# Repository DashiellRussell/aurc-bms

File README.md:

# AURC_BMS

Battery Management System for AURC (Australian Universities Rocket Competition).
Four-channel battery board set feeding two flight computers (FC1, FC2) and two pyro boards.
KiCad 10 project set.

## Layout

```
AURC_BMS/
├── libs/                     ← shared, single source of truth (all three boards point here)
│   ├── BMS.kicad_sym         ← symbols
│   ├── BMS.pretty/           ← footprints
│   └── 3dmodels/             ← .step / .wrl
├── docs/
│   ├── interconnect.md                ← the connector contract — READ THIS before touching a board edge
│   ├── architecture.md                ← full design rationale (living doc, currently v0.3)
│   └── board1_power_capture_plan.md   ← Board 1 schematic capture plan (sheets, netlist, BOM)
├── board1_power/             ← Board 1: USB-C, PD sink, 4× SY6970 smart charger, cells, ESP+I²C mux
├── board2_monitor/           ← Board 2: 64-LED gauge + driver, 4× pull-pin power-enable (spine)
├── board3_dist/              ← Board 3: passive fan-out to FC1+Pyro1 / FC2+Pyro2
└── _archive/                 ← previous single-board attempt (v0.1), kept for reference
```

Each `boardN_*/` is an independent KiCad project (`.kicad_pro` / `.kicad_sch` / `.kicad_pcb`) with
its own `sym-lib-table` + `fp-lib-table` that resolve the **shared** library at `../libs/` under
the nickname **`BMS`**. Add a part once in `libs/`; all three boards see it.

## Working on it

- **Before changing any board-to-board connector, edit `docs/interconnect.md` first.** It is the
  only thing keeping the three separately-laid-out boards mate-compatible.
- Add/edit symbols in `libs/BMS.kicad_sym`, footprints in `libs/BMS.pretty/`, 3D models in
  `libs/3dmodels/`. Don't make per-board copies — that defeats the single-source-of-truth setup.
- Open a board by opening its `boardN_*/boardN_*.kicad_pro`.

See `docs/architecture.md` for the full design (protection stack, charging, monitoring,
power-enable/safety, BOM, open items).

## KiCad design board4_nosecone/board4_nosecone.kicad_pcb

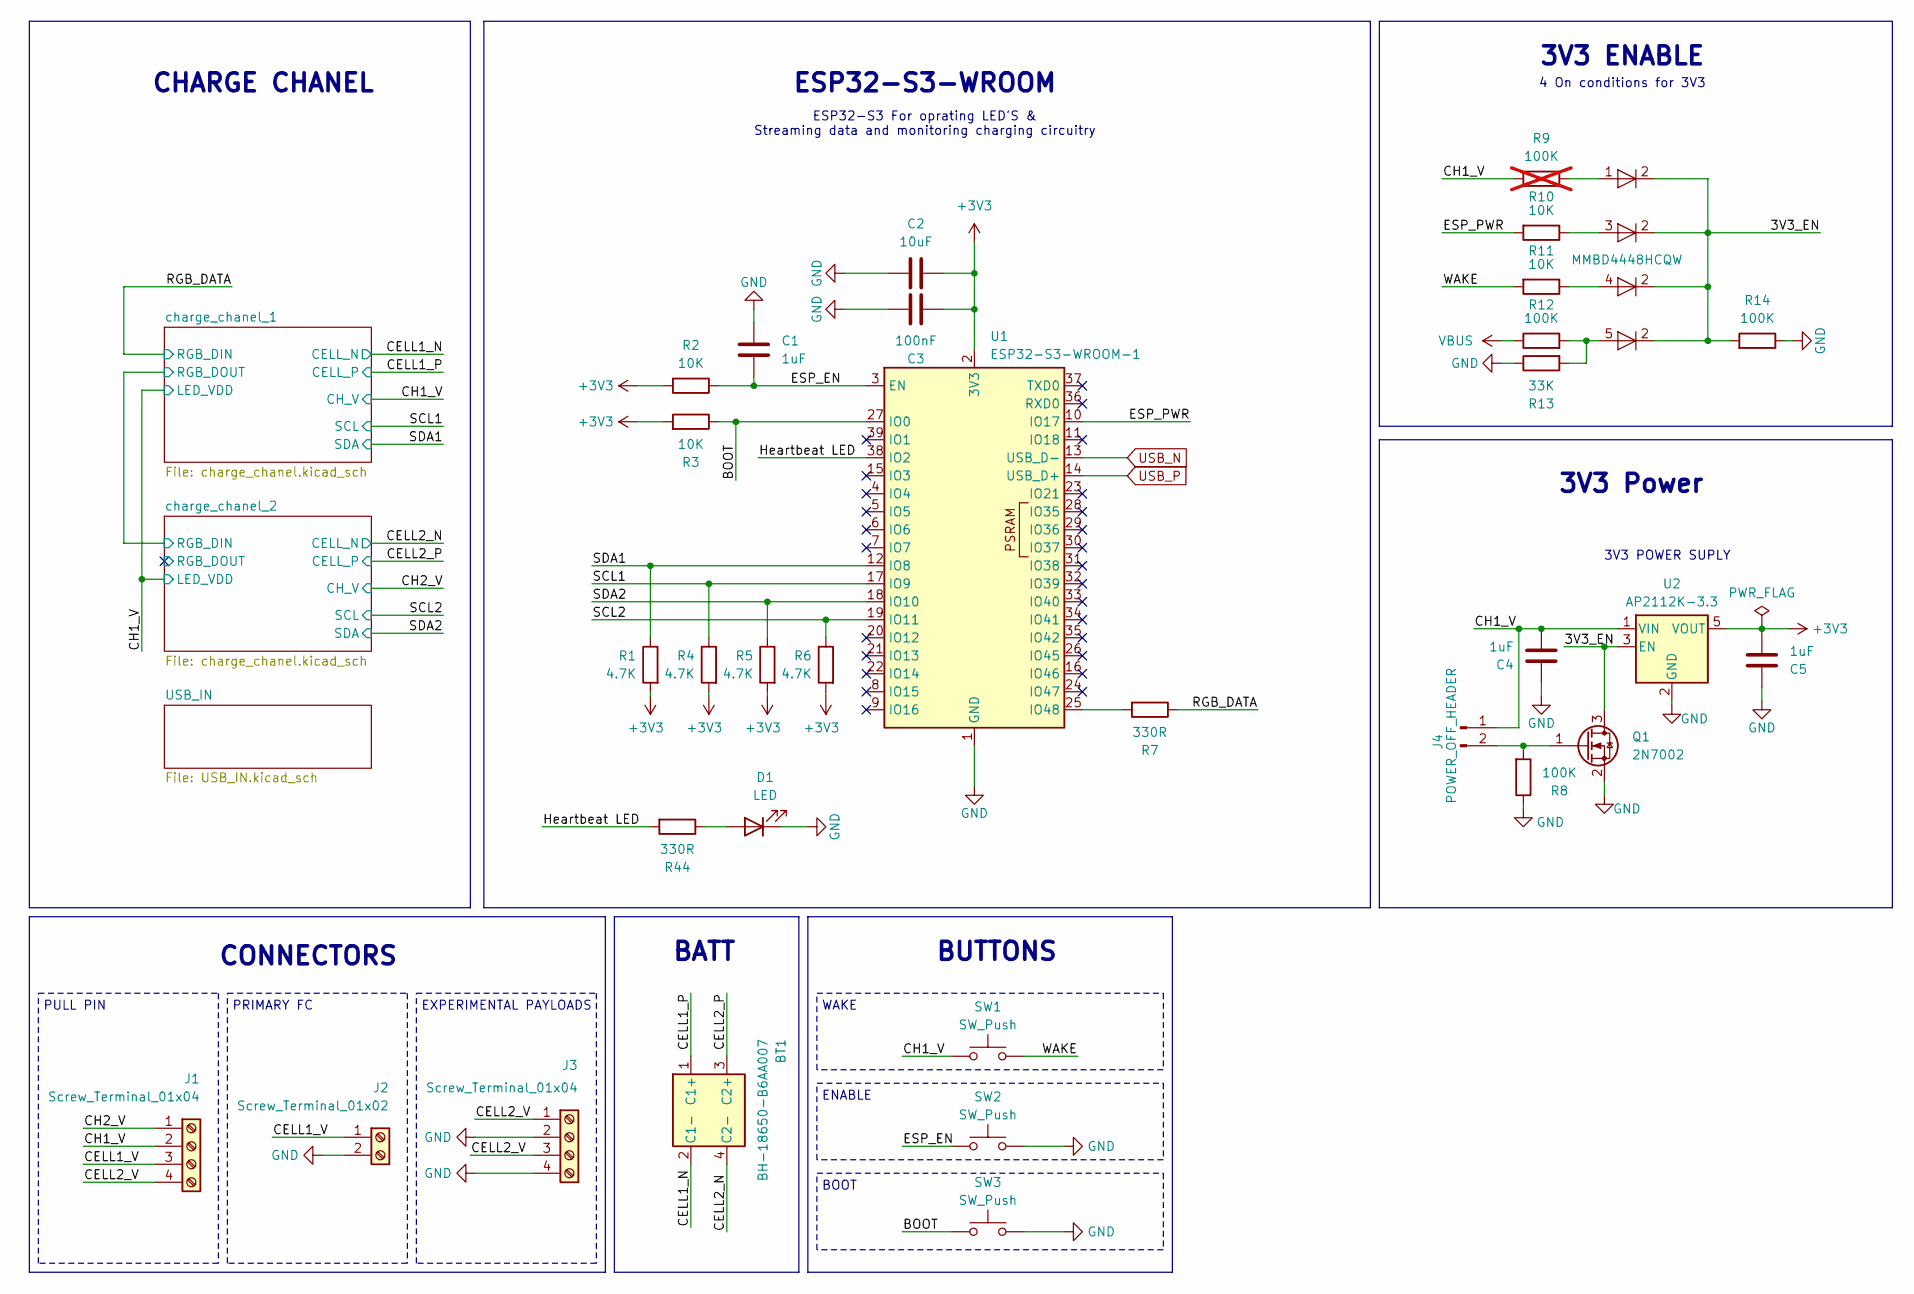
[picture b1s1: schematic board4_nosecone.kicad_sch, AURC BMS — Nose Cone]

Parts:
BT1: BH-18650-B6AA007
C1: 1uF; C_0603_1608Metric
C2: 10uF; C_0805_2012Metric
C3: 100nF; C_0805_2012Metric
C4, C5: 1uF; C_0805_2012Metric
D1: LED; LED_0603_1608Metric
D2: MMBD4448HCQW; SOT-353_SC-70-5
J1, J3: Screw_Terminal_01x04; TerminalBlock_Phoenix_PT-1,5-4-3.5-H_1x04_P3.50mm_Horizontal
J2: Screw_Terminal_01x02; TerminalBlock_Phoenix_PT-1,5-2-3.5-H_1x02_P3.50mm_Horizontal
J4: POWER_OFF_HEADER; PinHeader_1x02_P2.54mm_Horizontal
Q1: 2N7002; SOT-23
R1, R4, R5, R6: 4.7K; R_0603_1608Metric
R2, R3, R10, R11: 10K; R_0603_1608Metric
R7, R44: 330R; R_0603_1608Metric
R8, R12, R14: 100K; R_0603_1608Metric
R9: 100K; R_0603_1608Metric; not fitted
R13: 33K; R_0603_1608Metric
SW1, SW2, SW3: SW_Push; SW_Push_1P1T_NO_CK_KMR2
U1: ESP32-S3-WROOM-1
U2: AP2112K-3.3; SOT-23-5

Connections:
+3V3: C2.1, C3.1, C5.1, R1.2, R2.2, R3.2, R4.2, R5.2, R6.2, U1.2 (3V3), U2.5 (VOUT); also elsewhere on the board
/3V3_EN: D2.2 (K), Q1.3 (D), R14.2, U2.3 (EN)
/BOOT: R3.1, SW3.1, U1.27 (IO0)
/CELL1_N: BT1.2 (C1-); also elsewhere on the board
/CELL1_P: BT1.1 (C1+); also elsewhere on the board
/CELL1_V: J1.3, J2.1
/CELL2_N: BT1.4 (C2-); also elsewhere on the board
/CELL2_P: BT1.3 (C2+); also elsewhere on the board
/CELL2_V: J1.4, J3.1, J3.3
/CH1_V: C4.1, J1.2, J4.1, R9.1, SW1.1, U2.1 (VIN); also elsewhere on the board
/CH2_V: J1.1; also elsewhere on the board
/ESP_EN: C1.2, R2.1, SW2.1, U1.3 (EN)
/ESP_PWR: R10.2, U1.10 (IO17)
/Heartbeat LED: R44.2, U1.38 (IO2)
/RGB_DATA: R7.1; also elsewhere on the board
/SCL1: R4.1, U1.17 (IO9); also elsewhere on the board
/SCL2: R6.1, U1.19 (IO11); also elsewhere on the board
/SDA1: R1.1, U1.12 (IO8); also elsewhere on the board
/SDA2: R5.1, U1.18 (IO10); also elsewhere on the board
/WAKE: R11.2, SW1.2
GND: C1.1, C2.2, C3.2, C4.2, C5.2, D1.1 (K), J2.2, J3.2, J3.4, Q1.2 (S), R8.1, R13.1, R14.1, SW2.2, SW3.2, U1.1 (GND), U1.40 (GND), U1.41 (GND), U2.2 (GND); also elsewhere on the board
unnamed: D1.2 (A), R44.1
unnamed: D2.1 (A), R9.2
unnamed: D2.3 (A), R10.1
unnamed: D2.4 (A), R11.1
unnamed: D2.5 (A), R12.2, R13.2
unnamed: J4.2, Q1.1 (G), R8.2
unnamed: R7.2, U1.25 (IO48)
USB_N: U1.13 (USB_D-); also elsewhere on the board
USB_P: U1.14 (USB_D+); also elsewhere on the board
VBUS: R12.1; also elsewhere on the board

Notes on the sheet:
BUTTONS
CHARGE CHANEL
3V3 Power
4 On conditions for 3V3
ESP32-S3 For oprating LED'S & Streaming data and monitoring charging circuitry
ESP32-S3-WROOM
ENABLE
3V3 POWER SUPLY
PRIMARY FC
3V3 ENABLE
EXPERIMENTAL PAYLOADS
BATT
CONNECTORS
PULL PIN
BOOT
WAKE

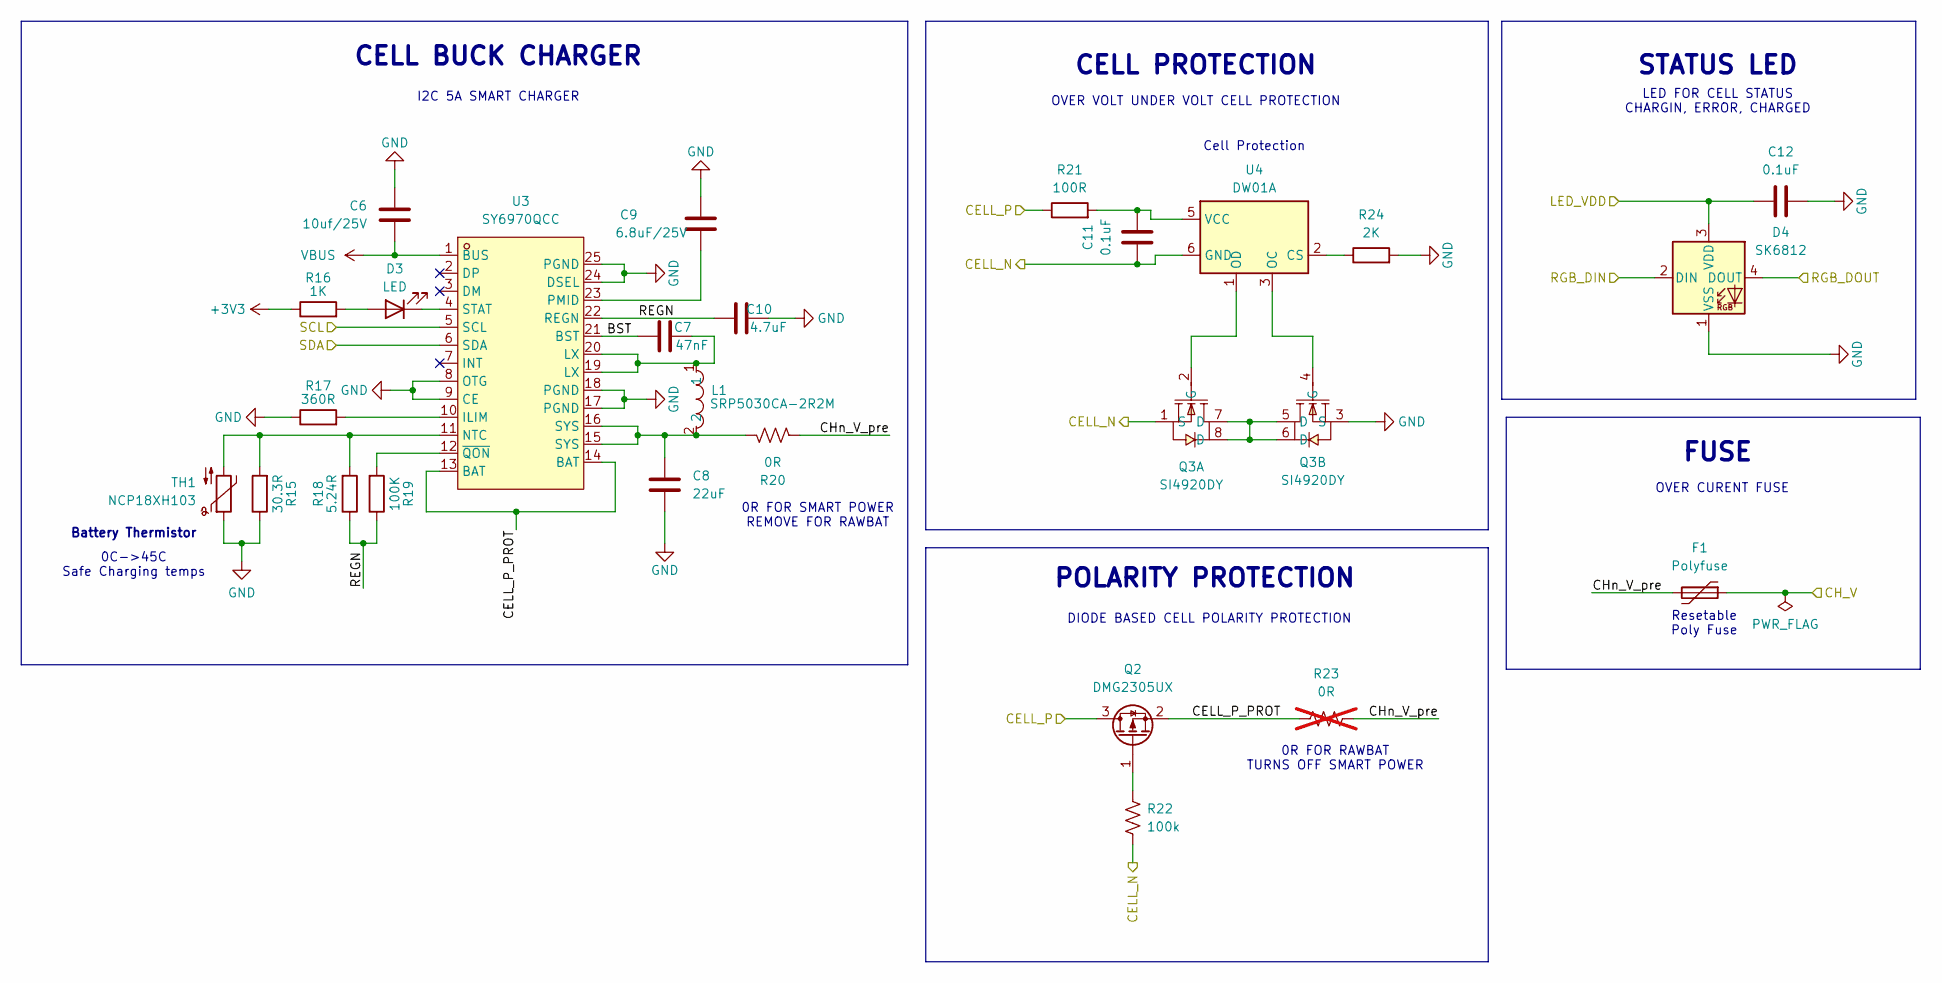
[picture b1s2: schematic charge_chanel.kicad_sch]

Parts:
C6: 10uf/25V; C_1206_3216Metric
C7: 47nF; C_0805_2012Metric
C8: 22uF; C_1206_3216Metric
C9: 6.8uF/25V; C_0805_2012Metric
C10: 4.7uF; C_0805_2012Metric
C11, C12: 0.1uF; C_0603_1608Metric
D3: LED; LED_0603_1608Metric
D4: SK6812; LED_SK6812_PLCC4_5.0x5.0mm_P3.2mm
F1: Polyfuse; Fuse_1812_4532Metric
L1: SRP5030CA-2R2M; IND-SMD_L5.5-W5.3; MPN SRP5030CA-2R2M; LCSC Part C2046809
Q2: DMG2305UX; SOT-23
Q3: SI4920DY; SOIC-8_L4.9-W3.9-P1.27-LS6.2-BL; MPN SI4920DY; LCSC Part C3289759
R15: 30.3R; R_0603_1608Metric
R16: 1K; R_0603_1608Metric
R17: 360R; R_0603_1608Metric
R18: 5.24R; R_0603_1608Metric
R19: 100K; R_0603_1608Metric
R20: 0R; R_2010_5025Metric
R21: 100R; R_0603_1608Metric
R22: 100k; R_0603_1608Metric
R23: 0R; R_2010_5025Metric; not fitted
R24: 2K; R_0603_1608Metric
TH1: NCP18XH103; R_0603_1608Metric
U3: SY6970QCC; QFN-24_L4.0-W4.0-P0.50-TL-EP2.7; MPN SY6970QCC; LCSC Part C5357542
U4: DW01A; SOT-23-6

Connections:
+3V3: R16.1; also elsewhere on the board
/CELL1_N: C11.1, Q3.1 (S), R22.1, U4.6 (GND); also elsewhere on the board
/CELL1_P: Q2.3 (D), R21.1; also elsewhere on the board
/CH1_V: C12.2, D4.3 (VDD), F1.1; also elsewhere on the board
/RGB_DATA: D4.2 (DIN); also elsewhere on the board
/SCL1: U3.5 (SCL); also elsewhere on the board
/SDA1: U3.6 (SDA); also elsewhere on the board
/charge_chanel_1/BST: C7.2, U3.21 (BST)
/charge_chanel_1/CELL_P_PROT: Q2.2 (S), R23.2, U3.13 (BAT), U3.14 (BAT)
/charge_chanel_1/CHn_V_pre: F1.2, R20.1, R23.1
/charge_chanel_1/REGN: C10.2, R18.1, R19.1, U3.22 (REGN)
/charge_chanel_1/RGB_DOUT: D4.4 (DOUT); also elsewhere on the board
GND: C6.1, C8.2, C9.1, C10.1, C12.1, D4.1 (VSS), Q3.3 (S), R15.1, R17.1, R24.2, TH1.1, U3.8 (OTG), U3.9 (CE), U3.17 (PGND), U3.18 (PGND), U3.24 (DSEL), U3.25 (PGND); also elsewhere on the board
unnamed: C7.1, L1.1, U3.19 (LX), U3.20 (LX)
unnamed: C8.1, L1.2, R20.2, U3.15 (SYS), U3.16 (SYS)
unnamed: D3.2 (A), R16.2
unnamed: D3.1 (K), U3.4 (STAT)
unnamed: Q2.1 (G), R22.2
unnamed: Q3.5 (D), Q3.6 (D), Q3.7 (D), Q3.8 (D)
unnamed: Q3.2 (G), U4.1 (OD)
unnamed: Q3.4 (G), U4.3 (OC)
unnamed: R17.2, U3.10 (ILIM)
unnamed: R15.2, R18.2, TH1.2, U3.11 (NTC)
unnamed: C9.2, U3.23 (PMID)
unnamed: R19.2, U3.12 (~QON)
unnamed: R24.1, U4.2 (CS)
unnamed: C11.2, R21.2, U4.5 (VCC)
VBUS: C6.2, U3.1 (BUS); also elsewhere on the board

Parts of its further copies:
C15: 10uf/25V; C_1206_3216Metric
C16: 47nF; C_0805_2012Metric
C17: 22uF; C_1206_3216Metric
C18: 6.8uF/25V; C_0805_2012Metric
C19: 4.7uF; C_0805_2012Metric
C20, C21: 0.1uF; C_0603_1608Metric
D6: LED; LED_0603_1608Metric
D7: SK6812; LED_SK6812_PLCC4_5.0x5.0mm_P3.2mm
F2: Polyfuse; Fuse_1812_4532Metric
L2: SRP5030CA-2R2M; IND-SMD_L5.5-W5.3; MPN SRP5030CA-2R2M; LCSC Part C2046809
Q4: DMG2305UX; SOT-23
Q5: SI4920DY; SOIC-8_L4.9-W3.9-P1.27-LS6.2-BL; MPN SI4920DY; LCSC Part C3289759
R34: 30.3R; R_0603_1608Metric
R35: 1K; R_0603_1608Metric
R36: 360R; R_0603_1608Metric
R37: 5.24R; R_0603_1608Metric
R38: 100K; R_0603_1608Metric
R39: 0R; R_2010_5025Metric
R40: 100R; R_0603_1608Metric
R41: 100k; R_0603_1608Metric
R42: 0R; R_2010_5025Metric; not fitted
R43: 2K; R_0603_1608Metric
TH2: NCP18XH103; R_0603_1608Metric
U7: SY6970QCC; QFN-24_L4.0-W4.0-P0.50-TL-EP2.7; MPN SY6970QCC; LCSC Part C5357542
U8: DW01A; SOT-23-6

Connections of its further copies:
+3V3: R35.1; also elsewhere on the board
/CELL2_N: C20.1, Q5.1 (S), R41.1, U8.6 (GND); also elsewhere on the board
/CELL2_P: Q4.3 (D), R40.1; also elsewhere on the board
/CH1_V: C21.2, D7.3 (VDD); also elsewhere on the board
/CH2_V: F2.1; also elsewhere on the board
/SCL2: U7.5 (SCL); also elsewhere on the board
/SDA2: U7.6 (SDA); also elsewhere on the board
/charge_chanel_1/RGB_DOUT: D7.2 (DIN); also elsewhere on the board
/charge_chanel_2/BST: C16.2, U7.21 (BST)
/charge_chanel_2/CELL_P_PROT: Q4.2 (S), R42.2, U7.13 (BAT), U7.14 (BAT)
/charge_chanel_2/CHn_V_pre: F2.2, R39.1, R42.1
/charge_chanel_2/REGN: C19.2, R37.1, R38.1, U7.22 (REGN)
/charge_chanel_2/RGB_DOUT: D7.4 (DOUT)
GND: C15.1, C17.2, C18.1, C19.1, C21.1, D7.1 (VSS), Q5.3 (S), R34.1, R36.1, R43.2, TH2.1, U7.8 (OTG), U7.9 (CE), U7.17 (PGND), U7.18 (PGND), U7.24 (DSEL), U7.25 (PGND); also elsewhere on the board
unnamed: C16.1, L2.1, U7.19 (LX), U7.20 (LX)
unnamed: C17.1, L2.2, R39.2, U7.15 (SYS), U7.16 (SYS)
unnamed: D6.2 (A), R35.2
unnamed: D6.1 (K), U7.4 (STAT)
unnamed: Q4.1 (G), R41.2
unnamed: Q5.5 (D), Q5.6 (D), Q5.7 (D), Q5.8 (D)
unnamed: Q5.2 (G), U8.1 (OD)
unnamed: Q5.4 (G), U8.3 (OC)
unnamed: R36.2, U7.10 (ILIM)
unnamed: R34.2, R37.2, TH2.2, U7.11 (NTC)
unnamed: C18.2, U7.23 (PMID)
unnamed: R38.2, U7.12 (~QON)
unnamed: R43.1, U8.2 (CS)
unnamed: C20.2, R40.2, U8.5 (VCC)
VBUS: C15.2, U7.1 (BUS); also elsewhere on the board

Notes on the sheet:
OVER VOLT UNDER VOLT CELL PROTECTION
CELL PROTECTION
0R FOR RAWBAT TURNS OFF SMART POWER
POLARITY PROTECTION
STATUS LED
Battery Thermistor
0C->45C Safe Charging temps
0R FOR SMART POWER REMOVE FOR RAWBAT
OVER CURENT FUSE
FUSE
Cell Protection
DIODE BASED CELL POLARITY PROTECTION
I2C 5A SMART CHARGER
CELL BUCK CHARGER
LED FOR CELL STATUS CHARGIN, ERROR, CHARGED
Resetable Poly Fuse

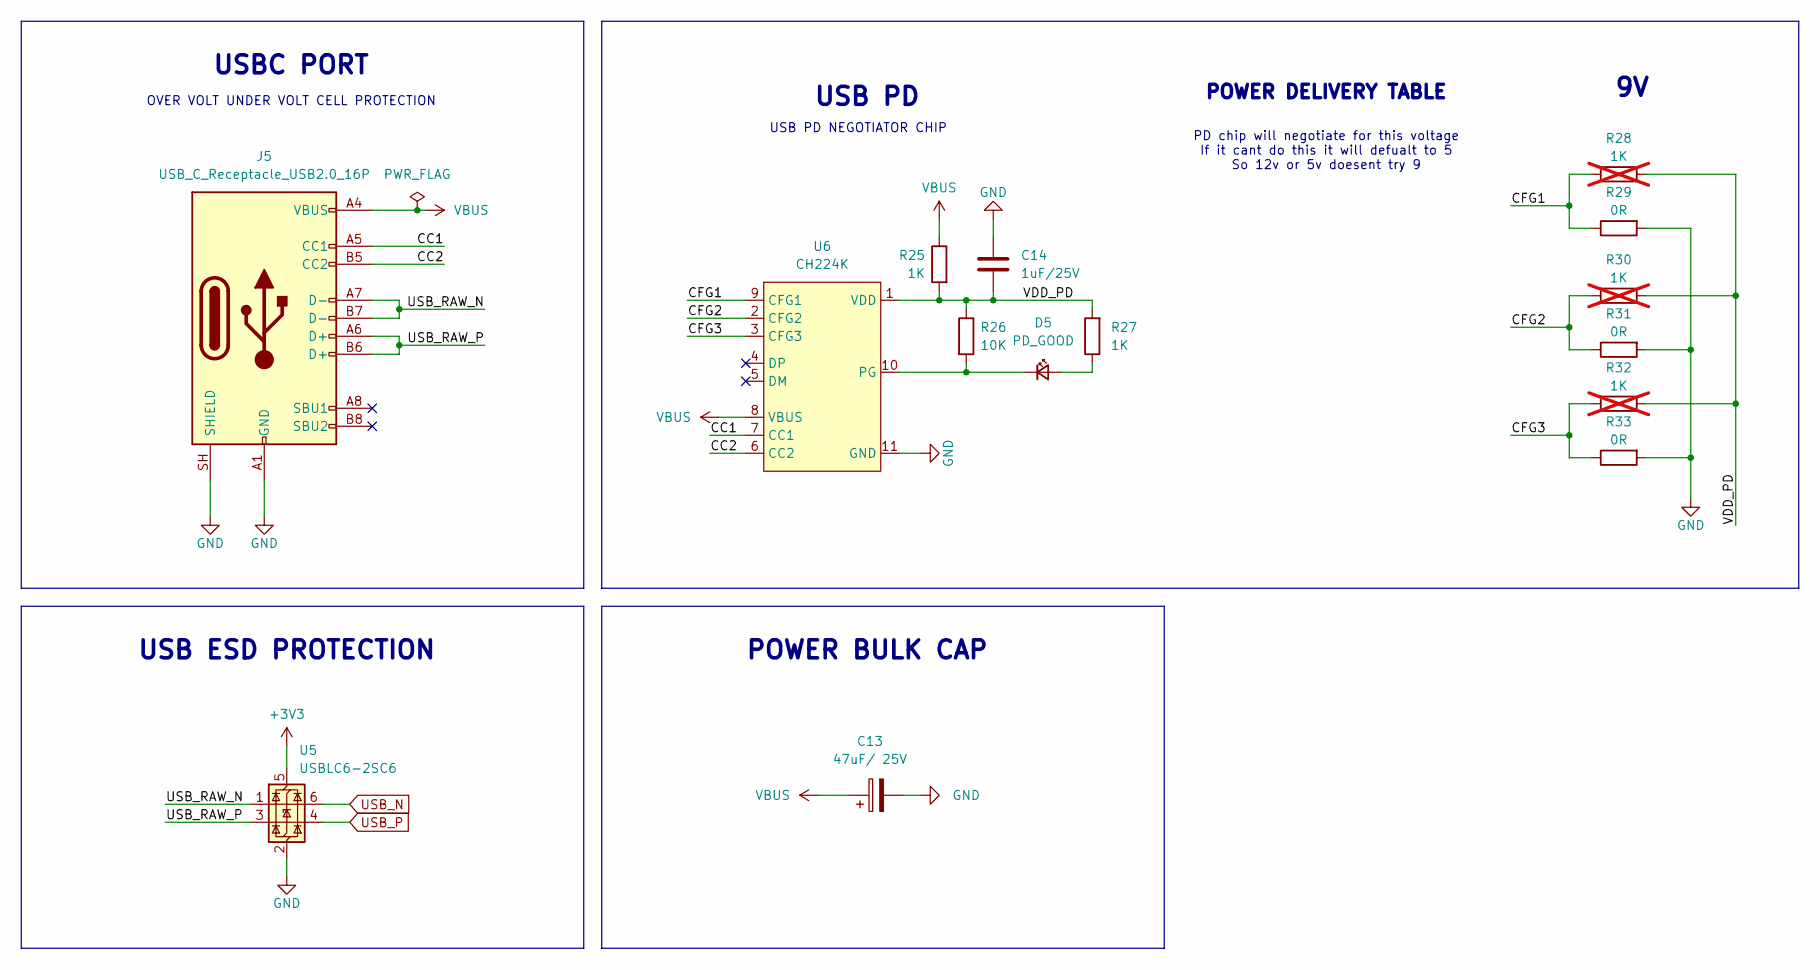
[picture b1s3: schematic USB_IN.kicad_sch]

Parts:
C13: 47uF/ 25V; CP_Elec_6.3x5.4
C14: 1uF/25V; C_0603_1608Metric
D5: PD_GOOD; LED_0603_1608Metric_Green
J5: USB_C_Receptacle_USB2.0_16P; USB_C_Receptacle_GCT_USB4105-xx-A_16P_TopMnt_Horizontal
R25: 1K; R_0805_2012Metric
R26: 10K; R_0603_1608Metric
R27: 1K; R_0603_1608Metric
R28, R30, R32: 1K; R_0805_2012Metric; not fitted
R29, R31, R33: 0R; R_0805_2012Metric
U5: USBLC6-2SC6; SOT-23-6
U6: CH224K; ESSOP-10_L4.9-W3.9-P1.0-LS6.0-TL-EP; MPN CH224K; LCSC Part C970725

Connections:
+3V3: U5.5 (VBUS); also elsewhere on the board
/USB_IN/CC1: J5.A5 (CC1), U6.7 (CC1)
/USB_IN/CC2: J5.B5 (CC2), U6.6 (CC2)
/USB_IN/CFG1: R28.2, R29.1, U6.9 (CFG1)
/USB_IN/CFG2: R30.2, R31.1, U6.2 (CFG2)
/USB_IN/CFG3: R32.2, R33.1, U6.3 (CFG3)
/USB_IN/USB_RAW_N: J5.A7 (D-), J5.B7 (D-), U5.1 (I/O1)
/USB_IN/USB_RAW_P: J5.A6 (D+), J5.B6 (D+), U5.3 (I/O2)
/USB_IN/VDD_PD: C14.2, R25.2, R26.1, R27.2, R28.1, R30.1, R32.1, U6.1 (VDD)
GND: C13.2, C14.1, J5.A1 (GND), J5.A12 (GND), J5.B1 (GND), J5.B12 (GND), J5.SH (SHIELD), R29.2, R31.2, R33.2, U5.2 (GND), U6.11 (GND); also elsewhere on the board
unnamed: D5.2 (A), R27.1
unnamed: D5.1 (K), R26.2, U6.10 (PG)
USB_N: U5.6 (I/O1); also elsewhere on the board
USB_P: U5.4 (I/O2); also elsewhere on the board
VBUS: C13.1, J5.A4 (VBUS), J5.A9 (VBUS), J5.B4 (VBUS), J5.B9 (VBUS), R25.1, U6.8 (VBUS); also elsewhere on the board

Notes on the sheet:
OVER VOLT UNDER VOLT CELL PROTECTION
USB ESD PROTECTION
USBC PORT
USB PD
POWER BULK CAP
PD chip will negotiate for this voltage If it cant do this it will defualt to 5 So 12v or 5v doesent try 9
USB PD NEGOTIATOR CHIP
POWER DELIVERY TABLE

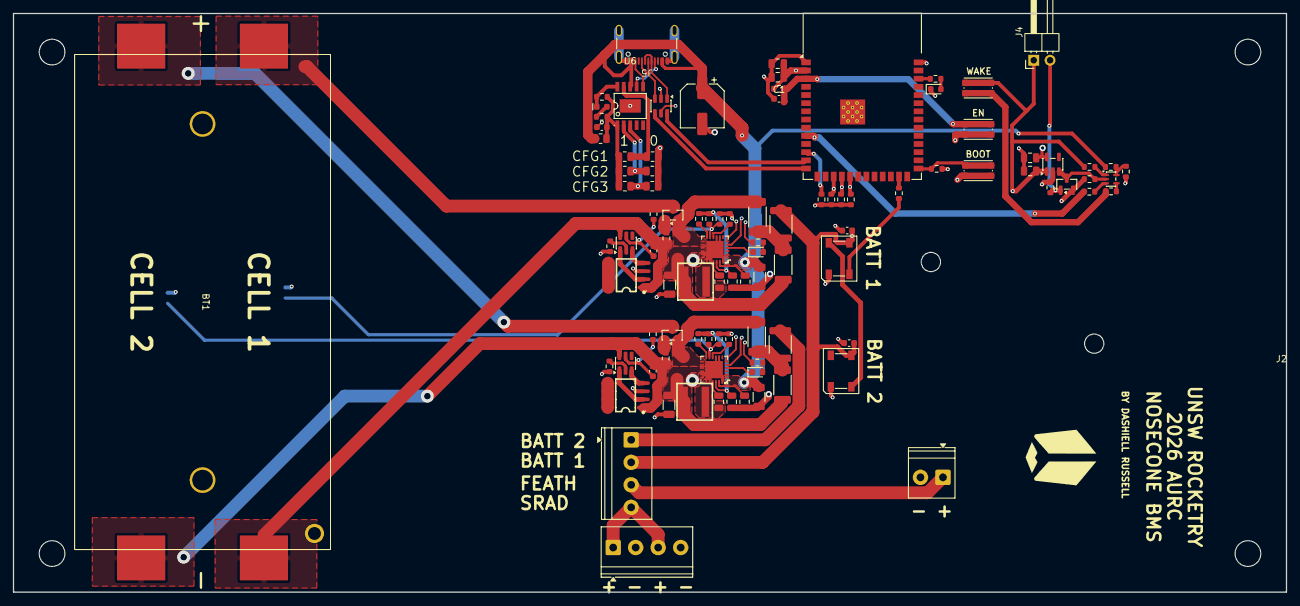
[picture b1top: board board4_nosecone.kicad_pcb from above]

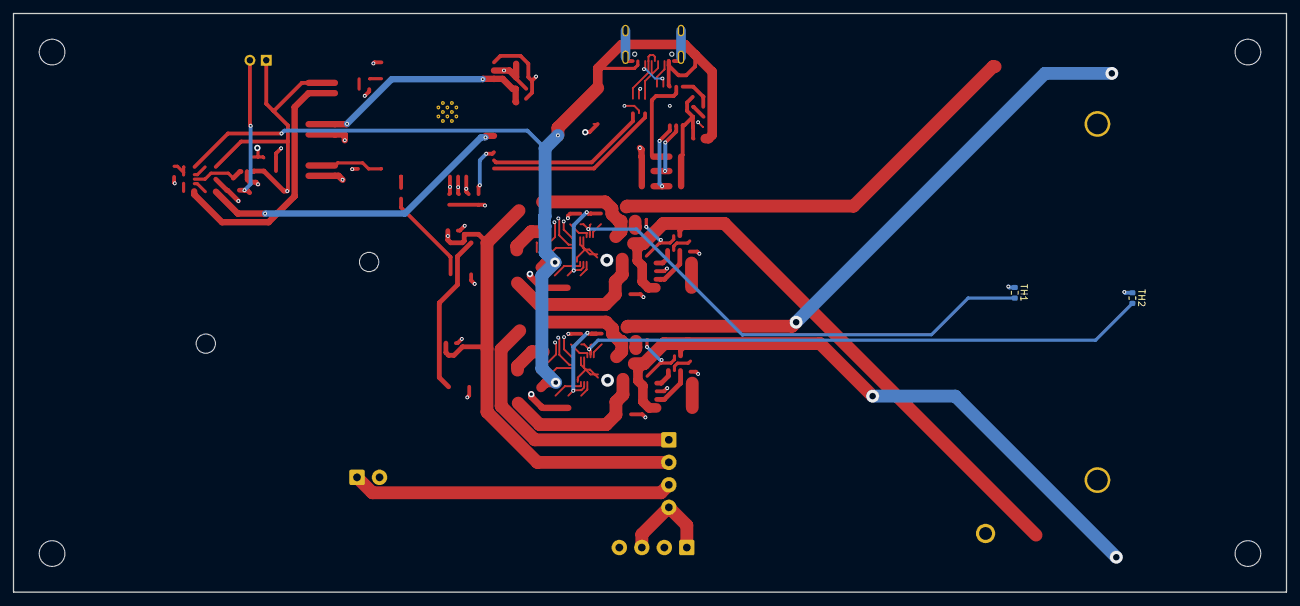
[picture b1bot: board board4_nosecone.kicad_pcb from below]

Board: 4 copper layers, 198.0 x 90.0 mm, 100 parts (2 on the bottom side), 78 nets.

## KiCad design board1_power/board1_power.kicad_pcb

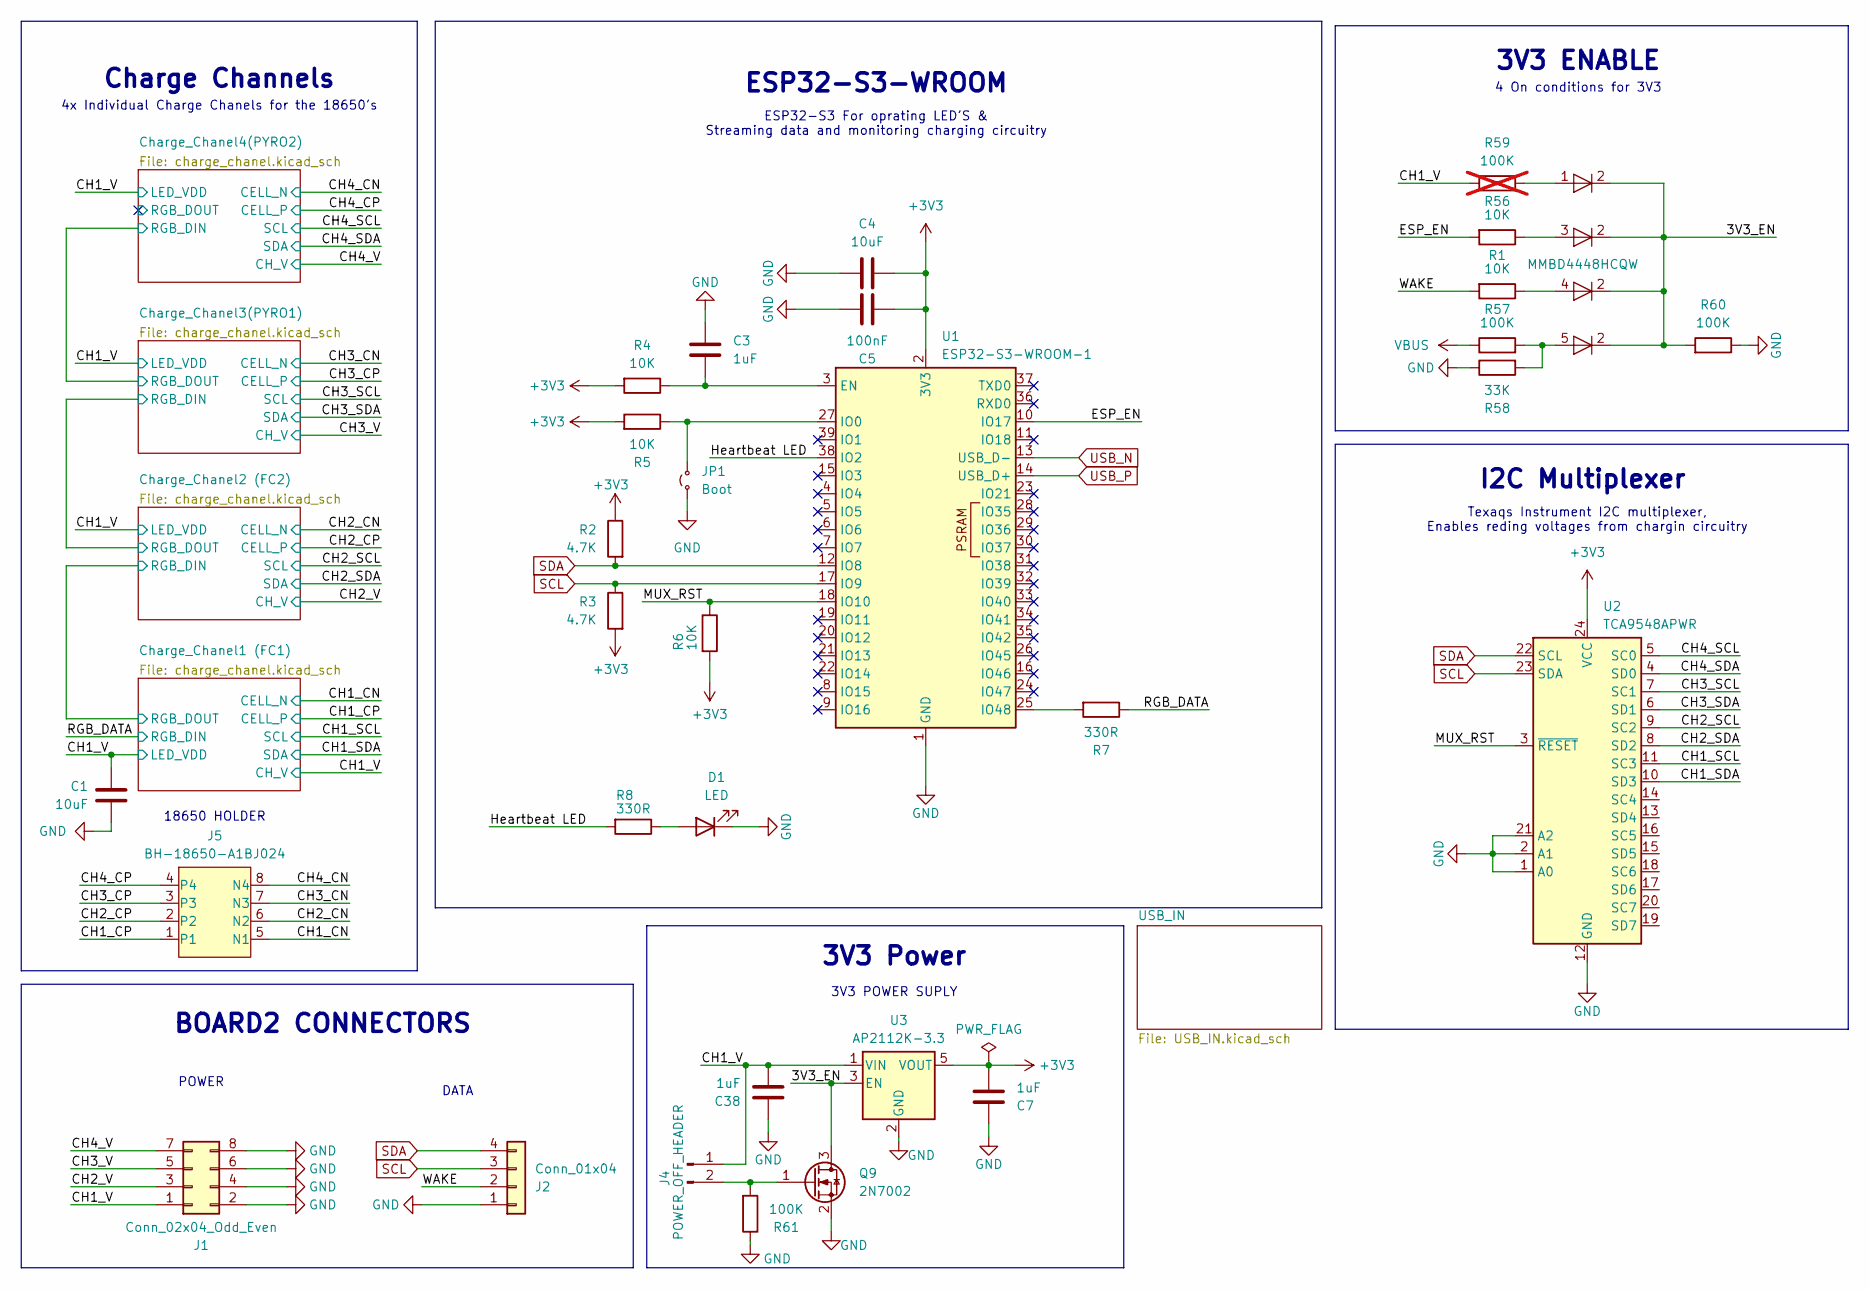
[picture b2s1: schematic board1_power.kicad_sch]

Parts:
C1, C4: 10uF; C_0805_2012Metric
C3: 1uF; C_0603_1608Metric
C5: 100nF; C_0805_2012Metric
C7, C38: 1uF; C_0805_2012Metric
D1: LED; LED_0603_1608Metric
D12: MMBD4448HCQW; SOT-353_SC-70-5
J1: Conn_02x04_Odd_Even; PinSocket_2x04_P2.54mm_Horizontal
J2: Conn_01x04; PinSocket_1x04_P2.54mm_Horizontal
J4: POWER_OFF_HEADER; PinHeader_1x02_P2.54mm_Horizontal
J5: BH-18650-A1BJ024
JP1: Boot; TestPoint_2Pads_Pitch2.54mm_Drill0.8mm
Q9: 2N7002; SOT-23
R1, R4, R5, R6, R56: 10K; R_0603_1608Metric
R2, R3: 4.7K; R_0603_1608Metric
R7, R8: 330R; R_0603_1608Metric
R57, R60, R61: 100K; R_0603_1608Metric
R58: 33K; R_0603_1608Metric
R59: 100K; R_0603_1608Metric; not fitted
U1: ESP32-S3-WROOM-1
U2: TCA9548APWR; TSSOP-24_4.4x7.8mm_P0.65mm
U3: AP2112K-3.3; SOT-23-5

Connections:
+3V3: C4.1, C5.1, C7.1, R2.1, R3.2, R4.2, R5.2, R6.2, U1.2 (3V3), U2.24 (VCC), U3.5 (VOUT); also elsewhere on the board
/3V3_EN: D12.2 (K), Q9.3 (D), R60.2, U3.3 (EN)
/CH1_CN: J5.5 (N1); also elsewhere on the board
/CH1_CP: J5.1; also elsewhere on the board
/CH1_SCL: U2.11 (SC3); also elsewhere on the board
/CH1_SDA: U2.10 (SD3); also elsewhere on the board
/CH1_V: C1.1, C38.1, J1.1, J4.1, R59.1, U3.1 (VIN); also elsewhere on the board
/CH2_CN: J5.6 (N2); also elsewhere on the board
/CH2_CP: J5.2; also elsewhere on the board
/CH2_SCL: U2.9 (SC2); also elsewhere on the board
/CH2_SDA: U2.8 (SD2); also elsewhere on the board
/CH2_V: J1.3; also elsewhere on the board
/CH3_CN: J5.7 (N3); also elsewhere on the board
/CH3_CP: J5.3; also elsewhere on the board
/CH3_SCL: U2.7 (SC1); also elsewhere on the board
/CH3_SDA: U2.6 (SD1); also elsewhere on the board
/CH3_V: J1.5; also elsewhere on the board
/CH4_CN: J5.8 (N4); also elsewhere on the board
/CH4_CP: J5.4; also elsewhere on the board
/CH4_SCL: U2.5 (SC0); also elsewhere on the board
/CH4_SDA: U2.4 (SD0); also elsewhere on the board
/CH4_V: J1.7; also elsewhere on the board
/ESP_EN: R56.2, U1.10 (IO17)
/Heartbeat LED: R8.2, U1.38 (IO2)
/MUX_RST: R6.1, U1.18 (IO10), U2.3 (~RESET)
/RGB_DATA: R7.1; also elsewhere on the board
/WAKE: J2.2, R1.2
GND: C1.2, C3.1, C4.2, C5.2, C7.2, C38.2, D1.1 (K), J1.2, J1.4, J1.6, J1.8, J2.1, JP1.1 (A), Q9.2 (S), R58.1, R60.1, R61.1, U1.1 (GND), U1.40 (GND), U1.41 (GND), U2.1 (A0), U2.2 (A1), U2.12 (GND), U2.21 (A2), U3.2 (GND); also elsewhere on the board
unnamed: D1.2 (A), R8.1
unnamed: D12.1 (A), R59.2
unnamed: D12.3 (A), R56.1
unnamed: D12.4 (A), R1.1
unnamed: D12.5 (A), R57.2, R58.2
unnamed: J4.2, Q9.1 (G), R61.2
unnamed: JP1.2 (B), R5.1, U1.27 (IO0)
unnamed: C3.2, R4.1, U1.3 (EN)
unnamed: R7.2, U1.25 (IO48)
SCL: J2.3, R3.1, U1.17 (IO9), U2.23 (SDA)
SDA: J2.4, R2.2, U1.12 (IO8), U2.22 (SCL)
USB_N: U1.13 (USB_D-); also elsewhere on the board
USB_P: U1.14 (USB_D+); also elsewhere on the board
VBUS: R57.1; also elsewhere on the board

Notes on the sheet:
ESP32-S3-WROOM
4x Individual Charge Chanels for the 18650's
Texaqs Instrument I2C multiplexer, Enables reding voltages from chargin circuitry
3V3 ENABLE
4 On conditions for 3V3
ESP32-S3 For oprating LED'S & Streaming data and monitoring charging circuitry
18650 HOLDER
BOARD2 CONNECTORS
3V3 POWER SUPLY
DATA
3V3 Power
Charge Channels
I2C Multiplexer
POWER
